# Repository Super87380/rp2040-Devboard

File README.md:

# RP2040 Devboard

This custom RP2040 Devboard features a built in 6 axis IMU, onboard LED, and 26 accessible GPIO Pins in a smaller package than a normal raspberry pi pico.

**Why did I make this?**\
I created this project to improve my PCB design skills, learn more about designing circuits around an MCU, and how to use an IMU. These skills I learnt will help me with my short term goal of making a device similar to a google home, and my long term goal of creating a thrust vector controlled rocket.

**What makes this devboard unique?**
- Built-in IMU which is not something ive seen
- It has a onboard LED that can be programmed to do anything you want (if that incudes turning on or off)
- Pretty compact package, I mean it is smaller than an official raspberry pi pico and has a built-in IMU

**How to assemble**\
Assembling this PCB is pretty straightforward if you have experience soldering SMD components. Or you can just order it assembled through JLCPCBA or other similar services.
I recommend getting a stencil with your PCB's so that it's easier to apply the thermal paste. It's also very helpful to have a hotplate or soldering oven but it is possible to solder the components with just a soldering iron or a hot air gun.

**How to Flash**\
Flashing the MCU is super simple, simply hold down the boot button and plug the board into your computer. It then shows up as a USB drive in file explorer in which you can then drag in your firmware of choice like the simple onboard LED blinking provided.

**BOM**\
Prices in USD
Hyperlink doesn't work, must copy and paste link into search bar.

| Part | Notes | Link | Quantity | Price Per Unit | Total |
| --- | --- | --- | --- | --- | --- |
| RP2040 | RP2040 MCU (only need 1, added 2 incase mistakes are made) | https://www.lcsc.com/product-detail/C2040.html | 2 | 0.9975 | 2.00 |
| W25Q16JVZPIQ | 16 Mbit (only need 1, added 2 incase mistakes are made) | https://www.lcsc.com/product-detail/C2456208.html | 2 | 1.92 | 3.84 |
| BMI323 | 6 Axis | https://www.lcsc.com/product-detail/C5368700.html | 1 | 3.26 | 3.26 |
| L327S120D11L | 12 Mhz | https://www.lcsc.com/product-detail/C5917263.html | 1 | 0.39 | 0.39 |
| TYPE-C16P3MDDGP073 | USB-C Receptacle | https://www.lcsc.com/product-detail/C2965608.html | 1 | 0.58 | 0.58 |
| P6E19A-602530-B1P | 19 Pin Male Headers, only need 2 (min 5) | https://www.lcsc.com/product-detail/C49451383.html | 5 | 0.0733 | 0.37 |
| 61300311121 | 3 Pin Male Headers, only need 1 (min 5) | https://www.lcsc.com/product-detail/C32713269.html | 5 | 0.0246 | 0.12 |
| CC0402KRX7R8BB104 | 0.1uf 0402 Capacitor, only need 13 (minimum 100) | https://www.lcsc.com/product-detail/C105883.html | 100 | 0.0073 | 0.73 |
| CGA0402X5R105K500GT | 1uf 0402 Capacitor, only need 2 (minimum 20) | https://www.lcsc.com/product-detail/C6119811.html | 20 | 0.0263 | 0.53 |
| TCC0603X5R106M350CT | 10uf 0603 Capacitor, only need 2 (minimum 10) | https://www.lcsc.com/product-detail/C22392391.html | 10 | 0.0542 | 0.54 |
| GJM1555C1H120GB01D | 12pf 0402 Capacitor, only need 2 (minimum 20) | https://www.lcsc.com/product-detail/C161305.html | 20 | 0.0306 | 0.61 |
| RC0402FR-075K1L | 5.1k 0402 Resistor, only need 2 (minimum 100) | https://www.lcsc.com/product-detail/C105872.html | 100 | 0.0025 | 0.25 |
| SR0402FR-7T10KL | 10k 0402 Resistor, only need 1 (minimum 20) | https://www.lcsc.com/product-detail/C854480.html | 20 | 0.024 | 0.48 |
| AC0402JR-074K7L | 4.7k 0402 Resistor, only need 2 (minimum 100) | https://www.lcsc.com/product-detail/C144709.html | 100 | 0.0023 | 0.23 |
| RC0402JR-071KL | 1k 0402 Resistor, only need 2 (minimum 100) | https://www.lcsc.com/product-detail/C105637.html | 100 | 0.0029 | 0.29 |
| RC0402FR-07270RL | 270 0402 Resistor, only need 1 (minimum 100) | https://www.lcsc.com/product-detail/C163474.html | 100 | 0.0019 | 0.19 |
| RCS040227R0FKED | 27 0402 Resistor, only need 2 (minimum 10) | https://www.lcsc.com/product-detail/C2100055.html | 10 | 0.0373 | 0.37 |
| CSL1104WBDW1 | 0603 White LED | https://www.lcsc.com/product-detail/C5603527.html | 1 | 0.311 | 0.31 |
| HX TS253015A2P 160gf | Boot Button, only need 1 (minimum 5) | https://www.lcsc.com/product-detail/C25168826.html | 5 | 0.1006 | 0.50 |
| PCB | Comes with 5 | | 1 | 2.1 | 2.10 |
| Solder Paste | Solder paste for soldering SMD components | https://www.amazon.ca/Chip-Quik-Smooth-Solder-Syringe/dp/B096BM9P32/ref=asc_df_B096BM9P32?mcid=c79d80be5a29307085398a6d21f548b6&tag=googleshopc0c-20&linkCode=df0&hvadid=716065606995&hvpos=&hvnetw=g&hvrand=17454086773741653853&hvpone=&hvptwo=&hvqmt=&hvdev=c&hvdvcmdl=&hvlocint=&hvlocphy=9208226&hvtargid=pla-1598852308533&psc=1&hvocijid=17454086773741653853-B096BM9P32-&hvexpln=0&gad_source=1 | 1 | 9.64 | 9.64 |
| | | | | Sub Total: | 27.33 |
| | | | | Shipping: | 8.68 |
| | | | | Total: | 36.01 |

PCB Quote\

This project was made possible through the funding of Hackclub and Forge.\
More information on the build and design process can be found in my [Forge Project](https://forge.hackclub.com/projects/2720)

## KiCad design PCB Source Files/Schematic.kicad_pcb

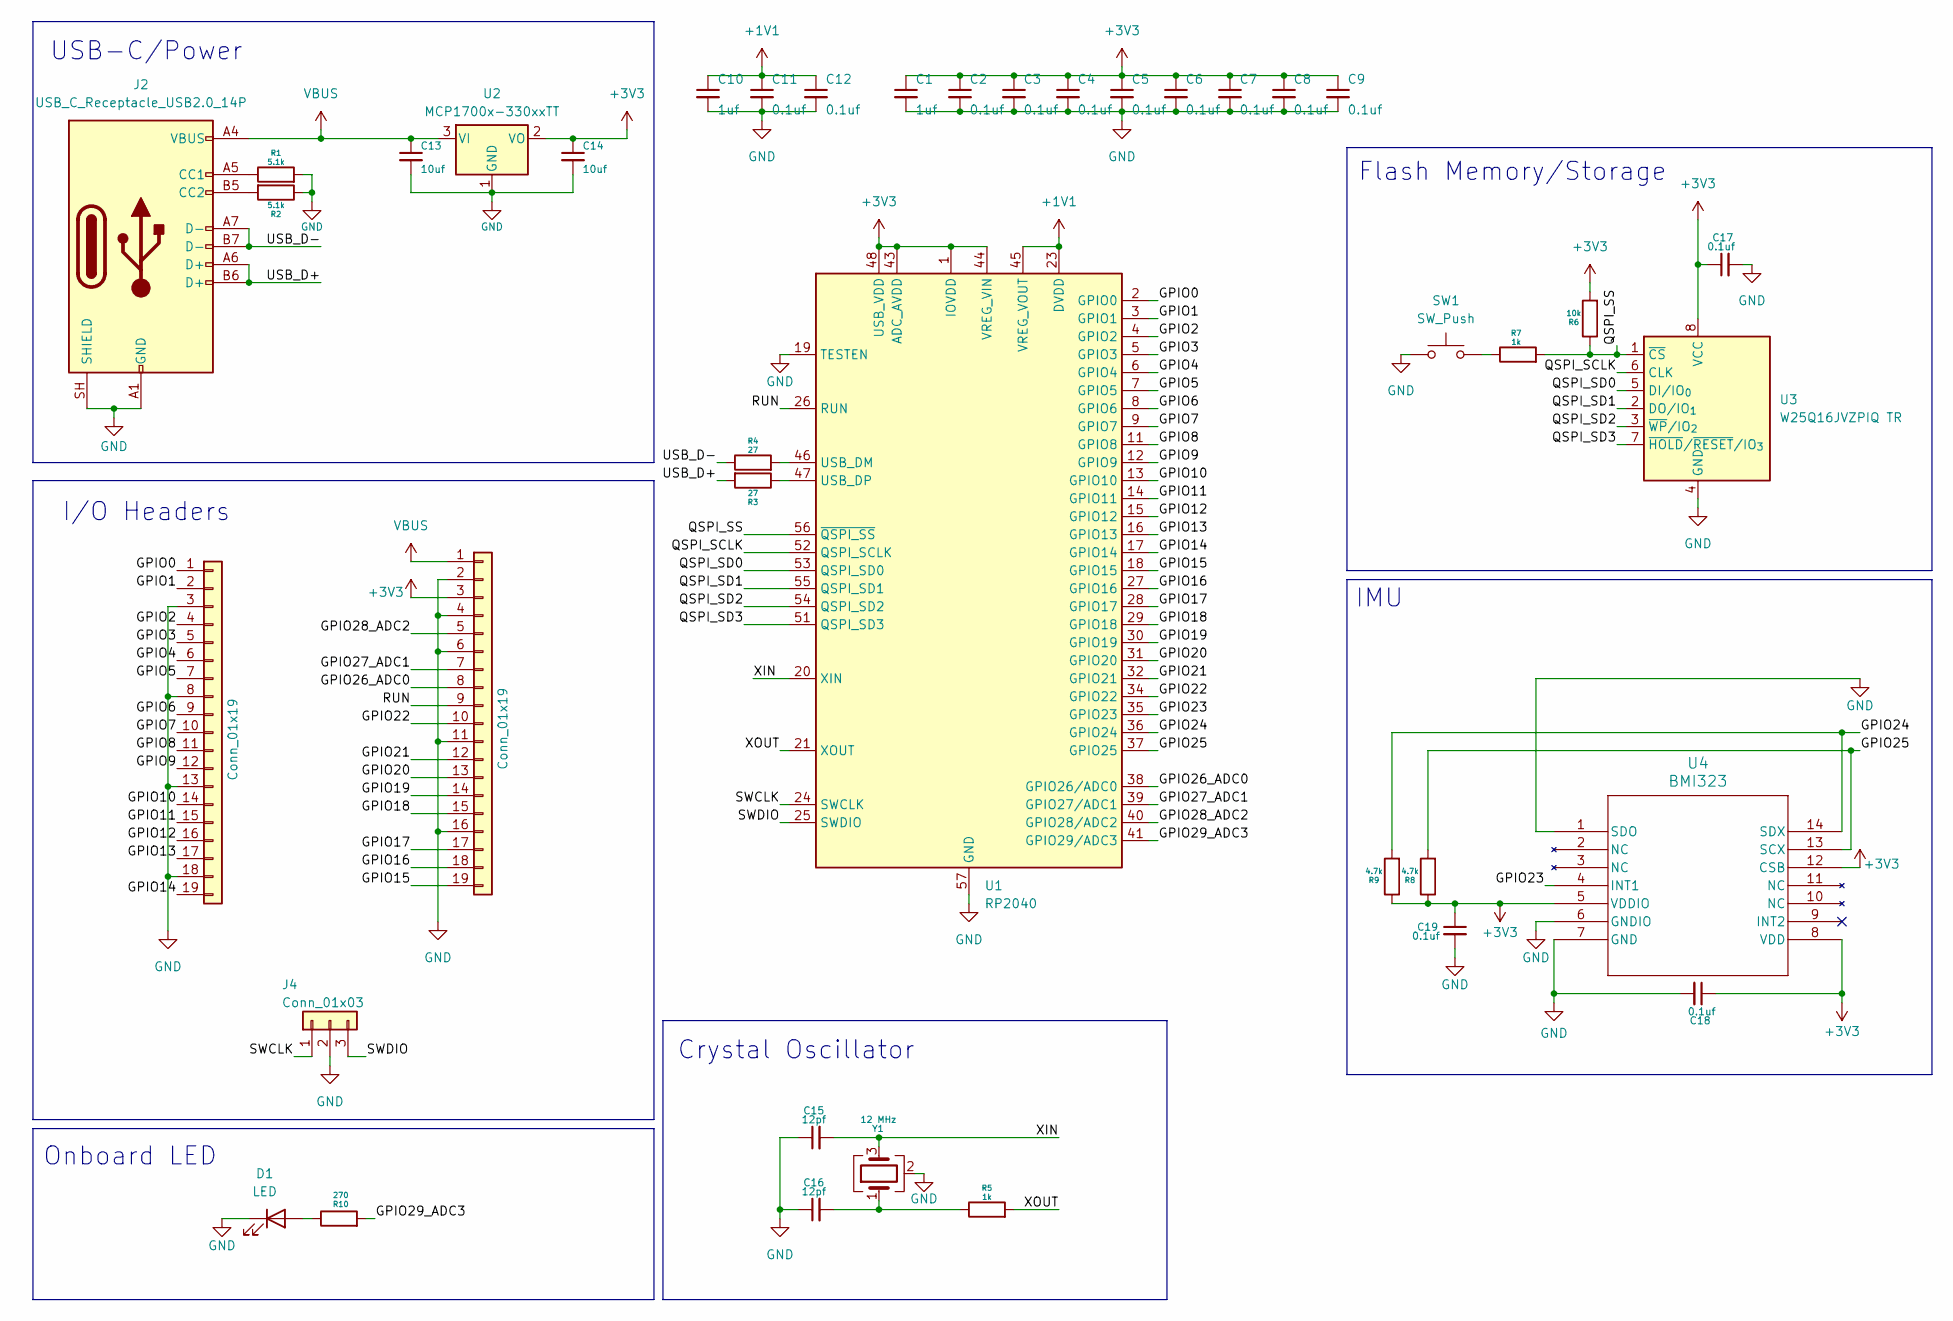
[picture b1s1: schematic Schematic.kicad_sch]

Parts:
C1, C10: 1uf; C_0402_1005Metric
C2, C3, C4, C5, C6, C7, C8, C9, C11, C12, C17, C18, C19: 0.1uf; C_0402_1005Metric
C13, C14: 10uf; C_0603_1608Metric
C15, C16: 12pf; C_0402_1005Metric
D1: LED; LED_0603_1608Metric
J2: USB_C_Receptacle_USB2.0_14P; TYPE-C-31-M-14
J4: Conn_01x03; PinHeader_1x03_P2.54mm_Vertical
J5, J6: Conn_01x19; PinHeader_1x19_P2.54mm_Vertical
R1, R2: 5.1k; R_0402_1005Metric
R3, R4: 27; R_0402_1005Metric
R5, R7: 1k; R_0402_1005Metric
R6: 10k; R_0402_1005Metric
R8, R9: 4.7k; R_0402_1005Metric
R10: 270; R_0402_1005Metric
SW1: SW_Push; SW_SPST_B3U-1000P
U1: RP2040; QFN-56-1EP_7x7mm_P0.4mm_EP3.2x3.2mm
U2: MCP1700x-330xxTT; SOT-23
U3: W25Q16JVZPIQ TR; Winbond_USON-8-1EP_3x2mm_P0.5mm_EP0.2x1.6mm
U4: BMI323; BMI323_BOS
Y1: 12 MHz; Crystal_SMD_3225-4Pin_3.2x2.5mm

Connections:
+1V1: C10.1, C11.1, C12.1, U1.23 (DVDD), U1.45 (VREG_VOUT), U1.50 (DVDD)
+3V3: C1.1, C2.1, C3.1, C4.1, C5.1, C6.1, C7.1, C8.1, C9.1, C14.1, C17.1, C18.1, C19.1, J6.3, R6.2, R8.1, R9.1, U1.1 (IOVDD), U1.10 (IOVDD), U1.22 (IOVDD), U1.33 (IOVDD), U1.42 (IOVDD), U1.43 (ADC_AVDD), U1.44 (VREG_VIN), U1.48 (USB_VDD), U1.49 (IOVDD), U2.2 (VO), U3.8 (VCC), U4.5 (VDDIO), U4.8 (VDD), U4.12 (CSB)
/GPIO0: J5.1, U1.2 (GPIO0)
/GPIO1: J5.2, U1.3 (GPIO1)
/GPIO2: J5.4, U1.4 (GPIO2)
/GPIO3: J5.5, U1.5 (GPIO3)
/GPIO4: J5.6, U1.6 (GPIO4)
/GPIO5: J5.7, U1.7 (GPIO5)
/GPIO6: J5.9, U1.8 (GPIO6)
/GPIO7: J5.10, U1.9 (GPIO7)
/GPIO8: J5.11, U1.11 (GPIO8)
/GPIO9: J5.12, U1.12 (GPIO9)
/GPIO10: J5.14, U1.13 (GPIO10)
/GPIO11: J5.15, U1.14 (GPIO11)
/GPIO12: J5.16, U1.15 (GPIO12)
/GPIO13: J5.17, U1.16 (GPIO13)
/GPIO14: J5.19, U1.17 (GPIO14)
/GPIO15: J6.19, U1.18 (GPIO15)
/GPIO16: J6.18, U1.27 (GPIO16)
/GPIO17: J6.17, U1.28 (GPIO17)
/GPIO18: J6.15, U1.29 (GPIO18)
/GPIO19: J6.14, U1.30 (GPIO19)
/GPIO20: J6.13, U1.31 (GPIO20)
/GPIO21: J6.12, U1.32 (GPIO21)
/GPIO22: J6.10, U1.34 (GPIO22)
/GPIO23: U1.35 (GPIO23), U4.4 (INT1)
/GPIO24: R9.2, U1.36 (GPIO24), U4.14 (SDX)
/GPIO25: R8.2, U1.37 (GPIO25), U4.13 (SCX)
/GPIO26_ADC0: J6.8, U1.38 (GPIO26/ADC0)
/GPIO27_ADC1: J6.7, U1.39 (GPIO27/ADC1)
/GPIO28_ADC2: J6.5, U1.40 (GPIO28/ADC2)
/GPIO29_ADC3: R10.2, U1.41 (GPIO29/ADC3)
/QSPI_SCLK: U1.52 (QSPI_SCLK), U3.6 (CLK)
/QSPI_SD0: U1.53 (QSPI_SD0), U3.5 (DI/IO_{0})
/QSPI_SD1: U1.55 (QSPI_SD1), U3.2 (DO/IO_{1})
/QSPI_SD2: U1.54 (QSPI_SD2), U3.3 (~WP/IO_{2})
/QSPI_SD3: U1.51 (QSPI_SD3), U3.7 (~HOLD/~RESET/IO_{3})
/QSPI_SS: R6.1, R7.2, U1.56 (~QSPI_SS), U3.1 (~CS)
/RUN: J6.9, U1.26 (RUN)
/SWCLK: J4.1, U1.24 (SWCLK)
/SWDIO: J4.3, U1.25 (SWDIO)
/USB_D+: J2.A6 (D+), J2.B6 (D+), R3.2
/USB_D-: J2.A7 (D-), J2.B7 (D-), R4.1
/XIN: C15.2, U1.20 (XIN), Y1.3
/XOUT: R5.2, U1.21 (XOUT)
GND: C1.2, C2.2, C3.2, C4.2, C5.2, C6.2, C7.2, C8.2, C9.2, C10.2, C11.2, C12.2, C13.2, C14.2, C15.1, C16.1, C17.2, C18.2, C19.2, D1.1 (K), J2.A1 (GND), J2.A12 (GND), J2.B1 (GND), J2.B12 (GND), J2.SH (SHIELD), J4.2, J5.3, J5.8, J5.13, J5.18, J6.2, J6.4, J6.6, J6.11, J6.16, R1.2, R2.1, SW1.1, U1.19 (TESTEN), U1.57 (GND), U2.1 (GND), U3.4 (GND), U4.1 (SDO), U4.6 (GNDIO), U4.7 (GND), Y1.2 (G), Y1.4 (G)
unnamed: C16.2, R5.1, Y1.1
unnamed: D1.2 (A), R10.1
unnamed: J2.A5 (CC1), R1.1
unnamed: J2.B5 (CC2), R2.2
unnamed: R7.1, SW1.2
unnamed: R4.2, U1.46 (USB_DM)
unnamed: R3.1, U1.47 (USB_DP)
VBUS: C13.1, J2.A4 (VBUS), J2.A9 (VBUS), J2.B4 (VBUS), J2.B9 (VBUS), J6.1, U2.3 (VI)

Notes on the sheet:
I/O Headers
Crystal Oscillator
Onboard LED
Flash Memory/Storage
IMU
USB-C/Power

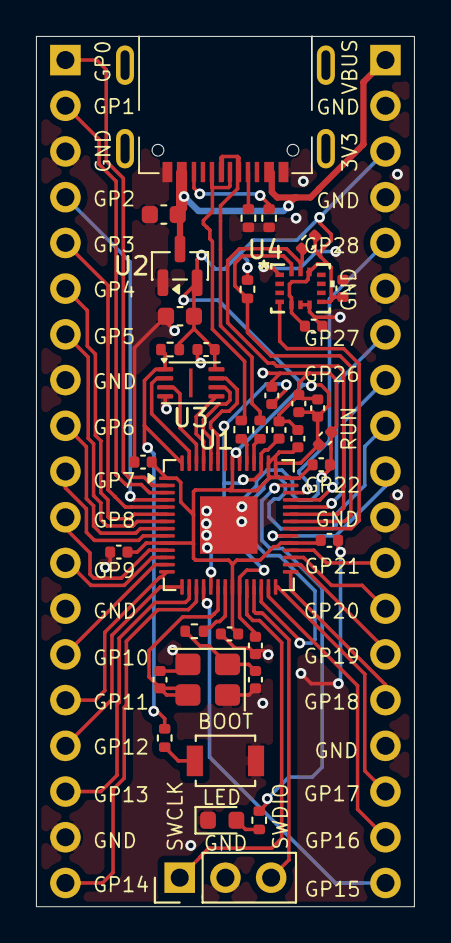
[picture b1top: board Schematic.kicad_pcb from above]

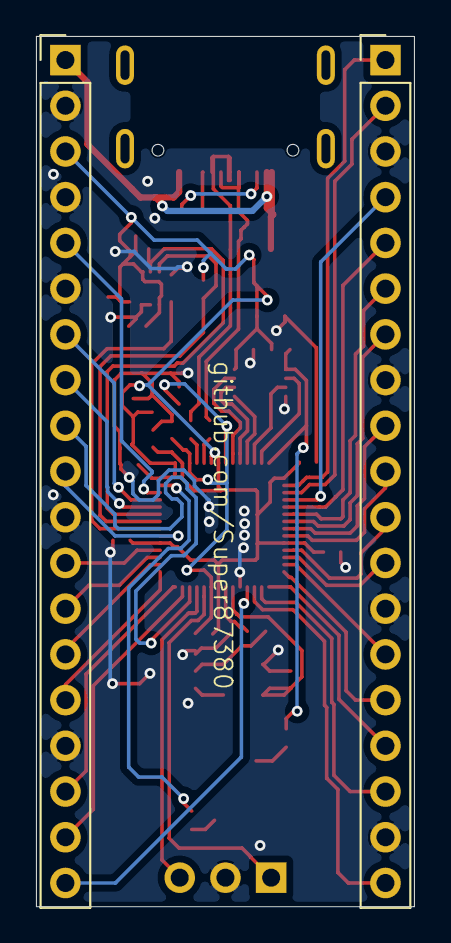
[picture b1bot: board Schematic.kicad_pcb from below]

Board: 2 copper layers, 21.0 x 48.3 mm, 40 parts (2 on the bottom side), 54 nets.
